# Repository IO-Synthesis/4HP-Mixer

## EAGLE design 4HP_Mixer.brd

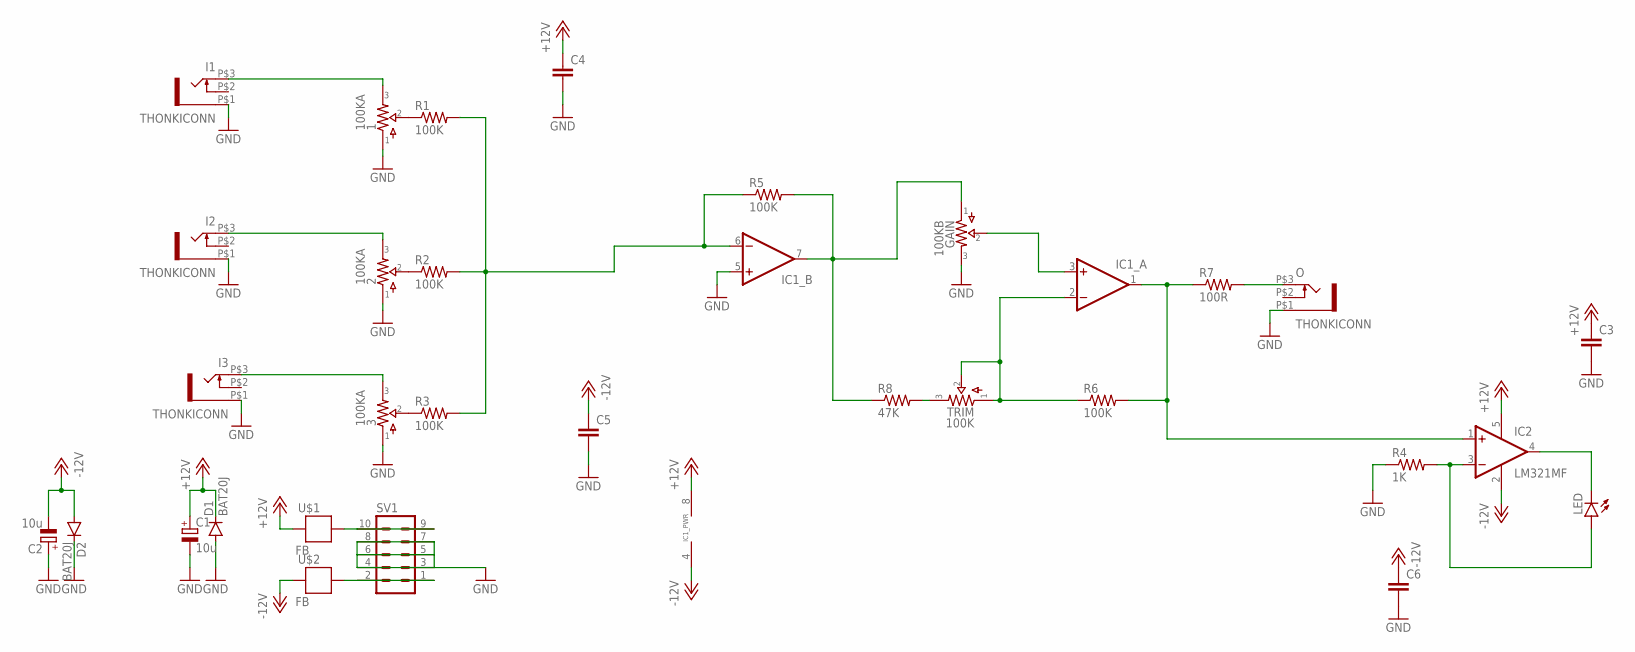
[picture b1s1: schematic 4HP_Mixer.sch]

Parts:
1, 2, 3: 100KA; 9MM_W/MOUNTS-2MMHOLES
C1, C2: 10u; CASE_B
C3, C4, C5, C6: CAP0603-CAP; 0603-CAP
D1, D2: BAT20J; SOD-123
GAIN: 100KB; 9MM_W/MOUNTS-2MMHOLES
I1, I2, I3: THONKICONN
IC1: DUALSMD; SO08
IC2: LM321MF; SOT23-5
LED: LED3MM
O: THONKICONN
R1, R2, R3, R5, R6: 100K; 0603-RES
R4: 1K; 0603-RES
R7: 100R; 0603-RES
R8: 47K; 0603-RES
SV1: EURO_POWER_HEADER
TRIM: 100K; PADS_SMALL
U$1, U$2: FB; 0603

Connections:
+12V: C1.+, C3.1, C4.1, D1.C, IC1.8 (V+), IC2.5 (V+), U$1.2
-12V: C2.-, C5.1, C6.1, D2.A, IC1.4 (V-), IC2.2 (V-), U$2.2
GND: 1.P$1 (1), 2.P$1 (1), 3.P$1 (1), C1.-, C2.+, C3.2, C4.2, C5.2, C6.2, D1.A, D2.C, GAIN.P$3 (3), I1.P$1 (5), I2.P$1 (5), I3.P$1 (5), IC1.5 (+IN), O.P$1 (5), R4.1, SV1.3, SV1.4, SV1.5, SV1.6, SV1.7, SV1.8
unnamed: IC2.3 (-IN), LED.A, R4.2
unnamed: IC2.4 (OUT), LED.K (C)
unnamed: IC1.2 (-IN), R6.1, TRIM.1, TRIM.2
unnamed: IC1.1 (OUT), IC2.1 (+IN), R6.2, R7.1
unnamed: GAIN.P$1 (1), IC1.7 (OUT), R5.2, R8.1
unnamed: O.P$3 (3), R7.2
unnamed: 1.P$2 (2), R1.1
unnamed: 2.P$2 (2), R2.1
unnamed: 3.P$2 (2), R3.1
unnamed: IC1.6 (-IN), R1.2, R2.2, R3.2, R5.1
unnamed: SV1.9, SV1.10, U$1.1
unnamed: SV1.1, SV1.2, U$2.1
unnamed: GAIN.P$2 (2), IC1.3 (+IN)
unnamed: R8.2, TRIM.3
unnamed: 1.P$3 (3), I1.P$3 (3)
unnamed: 2.P$3 (3), I2.P$3 (3)
unnamed: 3.P$3 (3), I3.P$3 (3)

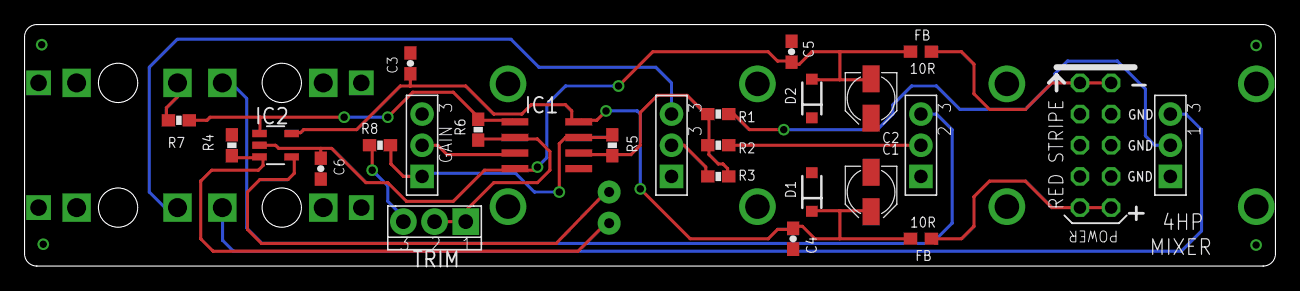
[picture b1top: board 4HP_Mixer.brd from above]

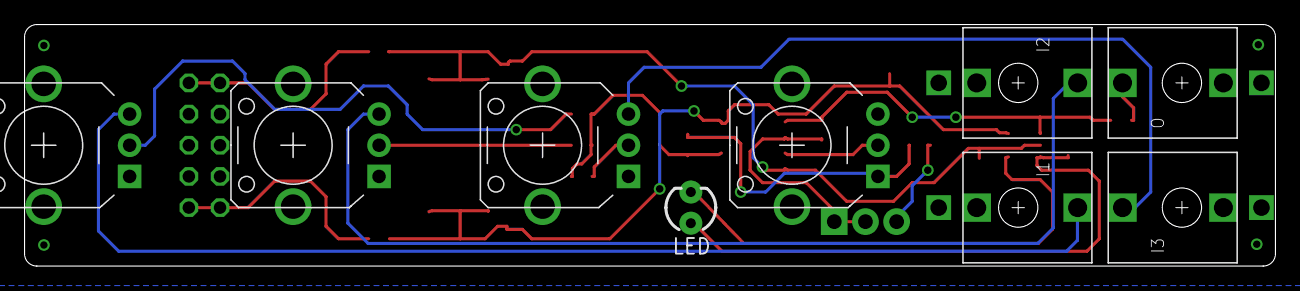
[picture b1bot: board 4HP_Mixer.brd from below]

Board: 2 copper layers, 101.9 x 19.7 mm, 31 parts (5 on the bottom side), 20 nets.

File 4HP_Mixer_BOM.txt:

4HP_Mixer_BOM

Qty Value      Device               Parts
4   100nF      CAP0603-CAP          C3, C4, C5, C6
1              DUALSMD              IC1
1              EURO_POWER_HEADER    SV1
1              Dual_Color_LED3MM    LED
1   1K         RESISTOR0603-RES     R4
2   10u        CAPACITOR_POL-CASE_B C1, C2
1   47K        RESISTOR0603-RES     R8
1   100K       POTSSMALL_PADS       TRIM
5   100K       RESISTOR0603-RES     R1, R2, R3, R5, R6
3   100KA      POTS9MM_MOUNTED      1, 2, 3
1   100KB      CD_POTS9MM_MOUNTED   GAIN
1   100R       RESISTOR0603-RES     R7
2   BAT20J     DIODESOD123          D1, D2
2   FB         FB                   U$1, U$2
1   LM321MF    LM321MF              IC2
4   THONKICONN THONKICONN           I1, I2, I3, O

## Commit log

2016-01-10 4HP-Mixer

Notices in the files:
parts and their libraries:
SparkFun-DiscreteSemi: Licensing: Creative Commons ShareAlike 4.0 International - https://creativecommons.org/licenses/by-sa/4.0
